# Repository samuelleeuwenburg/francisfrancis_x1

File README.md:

# FrancisFrancis X1

## Building the binary

Create a build folder, run cmake with your wifi info and build the project
```
$ mkdir firmware/build && cd firmware/build
$ cmake .. -DWIFI_SSID="network_name" -DWIFI_PASSWORD="password"
$ make -j4
```

## Running

Run openocd in the firmware folder
```
$ (sudo) openocd
```

Then use gdb to load the code
```
$ arm-none-eabi-gdb -q -x openocd.gdb build/francisfrancisx1.elf 
```

## Livebook

To run the notebook without installing Livebook you can use docker
```
$ docker run -p 8080:8080 -p 8081:8081 --pull always -u $(id -u):$(id -g) -v $(pwd):/data ghcr.io/livebook-dev/livebook
```

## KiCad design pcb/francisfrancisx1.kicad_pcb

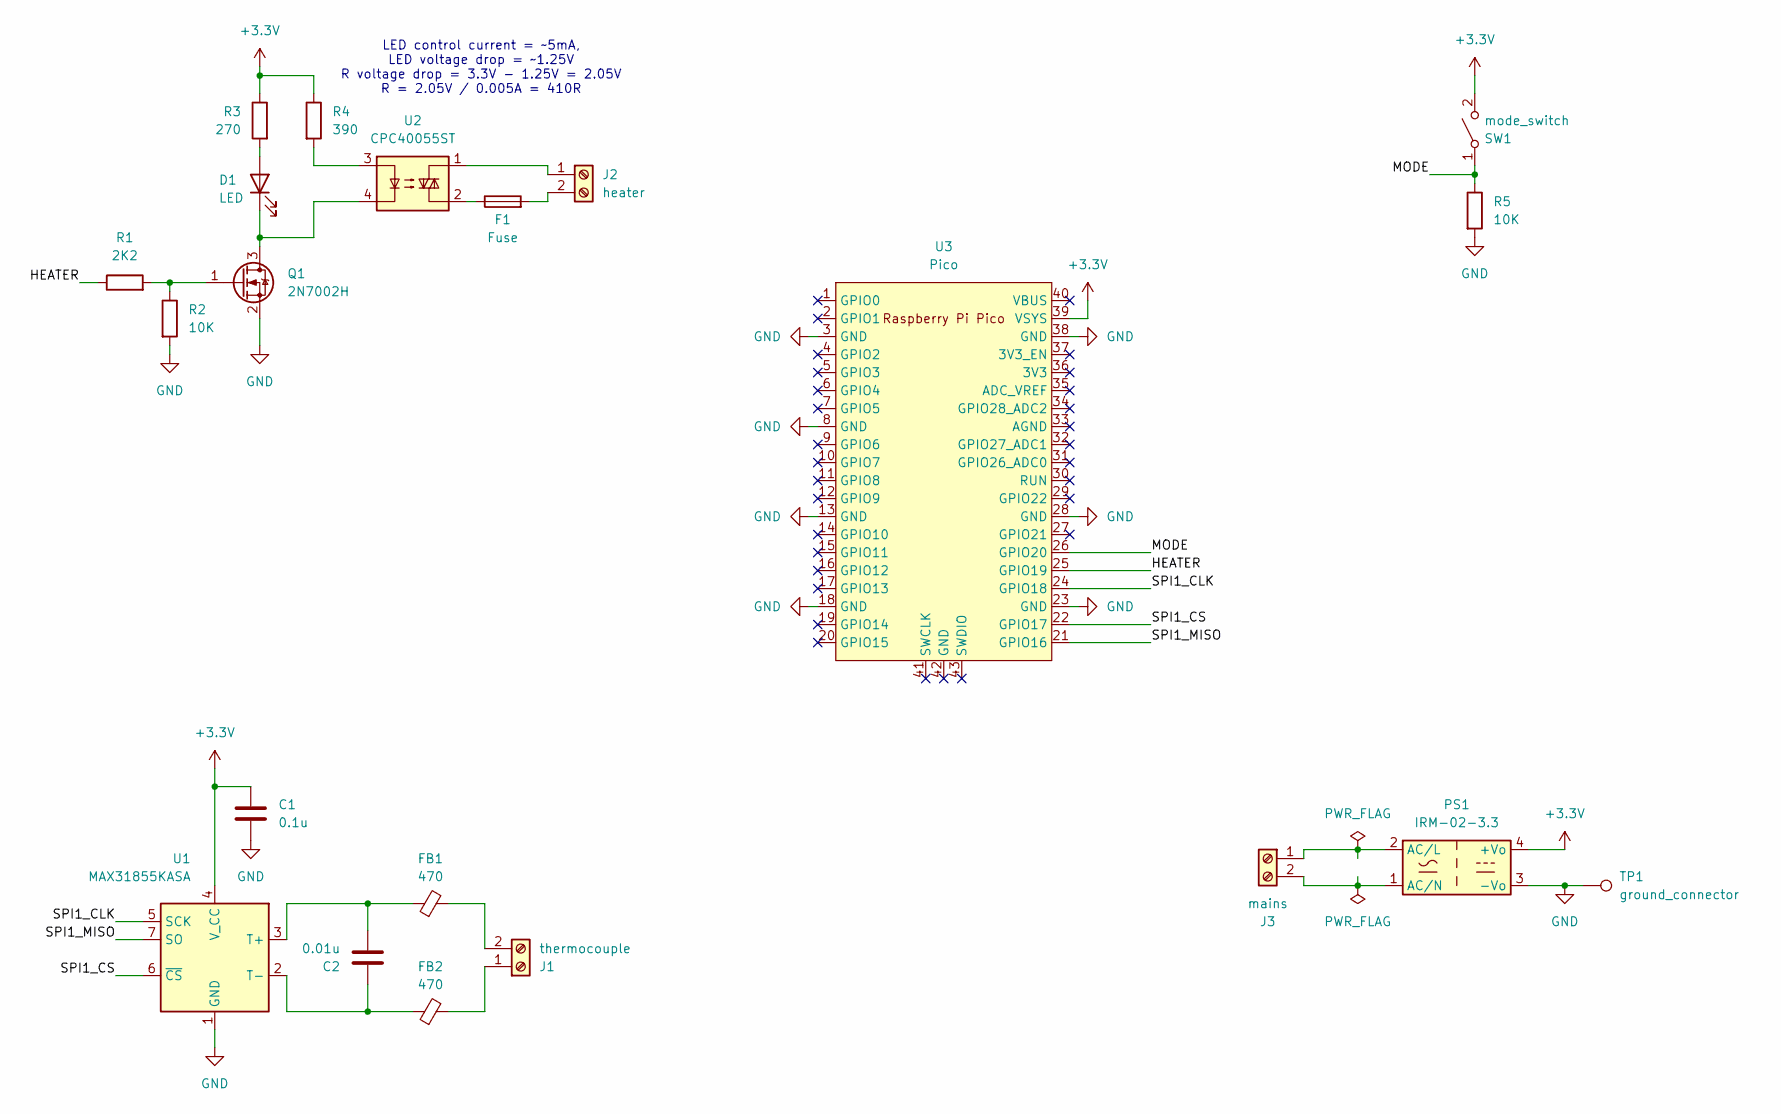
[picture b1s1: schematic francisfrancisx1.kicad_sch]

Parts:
C1: 0.1u; C_0805_2012Metric; MPN C0805X104K5RAC
C2: 0.01u; C_0805_2012Metric; MPN C0805Y103K5RACTU
D1: LED; LED_0805_2012Metric; MPN 150080AS75000
F1: Fuse; Fuseholder_Cylinder-5x20mm_Schurter_0031_8201_Horizontal_Op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; MPN 0031.8201.G
FB1, FB2: 470; R_0805_2012Metric; MPN 742792037
J1: thermocouple; TerminalBlock_Phoenix_MPT-0,5-2-2.54_1x02_P2.54mm_Horizontal; MPN 1725656
J2: heater; TerminalBlock_Phoenix_MKDS-1,5-2-5.08_1x02_P5.08mm_Horizont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; MPN 1715721
J3: mains; TerminalBlock_Phoenix_MKDS-1,5-2-5.08_1x02_P5.08mm_Horizont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; MPN 1715721
PS1: IRM-02-3.3; Converter_ACDC_MeanWell_IRM-02-xx_THT; MPN IRM-02-3.3
Q1: 2N7002H; SOT-23; MPN 2N7002HR
R1: 2K2; R_0805_2012Metric; MPN RT0805FRE132K2L
R2, R5: 10K; R_0805_2012Metric; MPN RT0805FRE1010KL
R3: 270; R_0805_2012Metric; MPN RT0805FRE07270RL
R4: 390; R_0805_2012Metric; MPN RT0805FRE07390RL
SW1: mode_switch; TerminalBlock_Phoenix_MPT-0,5-2-2.54_1x02_P2.54mm_Horizontal; MPN 1725656
TP1: ground_connector; MountingHole_2.2mm_M2_ISO7380_Pad
U1: MAX31855KASA; SOIC-8_3.9x4.9mm_P1.27mm; MPN MAX31855KASA+T
U2: CPC40055ST; MPN CPC40055ST
U3: Pico; RPi_Pico_SMD_TH; MPN SC0918

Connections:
+3.3V: C1.1, PS1.4 (+Vo), R3.1, R4.1, SW1.2 (B), U1.4 (V_CC), U3.39 (VSYS)
/HEATER: R1.1, U3.25 (GPIO19)
/MODE: R5.1, SW1.1 (A), U3.26 (GPIO20)
/SPI1_CLK: U1.5 (SCK), U3.24 (GPIO18)
/SPI1_CS: U1.6 (~CS), U3.22 (GPIO17)
/SPI1_MISO: U1.7 (SO), U3.21 (GPIO16)
GND: C1.2, PS1.3 (-Vo), Q1.2 (S), R2.2, R5.2, TP1.1, U1.1 (GND), U3.3 (GND), U3.8 (GND), U3.13 (GND), U3.18 (GND), U3.23 (GND), U3.28 (GND), U3.38 (GND)
unnamed: D1.2 (A), R3.2
unnamed: D1.1 (K), Q1.3 (D), U2.4
unnamed: F1.1, U2.2
unnamed: FB2.2, J1.1
unnamed: FB1.2, J1.2
unnamed: J2.1, U2.1
unnamed: F1.2, J2.2
unnamed: J3.1, PS1.2 (AC/L)
unnamed: J3.2, PS1.1 (AC/N)
unnamed: Q1.1 (G), R1.2, R2.1
unnamed: R4.2, U2.3
unnamed: C2.2, FB1.1, U1.3 (T+)
unnamed: C2.1, FB2.1, U1.2 (T-)

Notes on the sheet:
LED control current = ~5mA, LED voltage drop = ~1.25V R voltage drop = 3.3V - 1.25V = 2.05V R = 2.05V / 0.005A = 410R

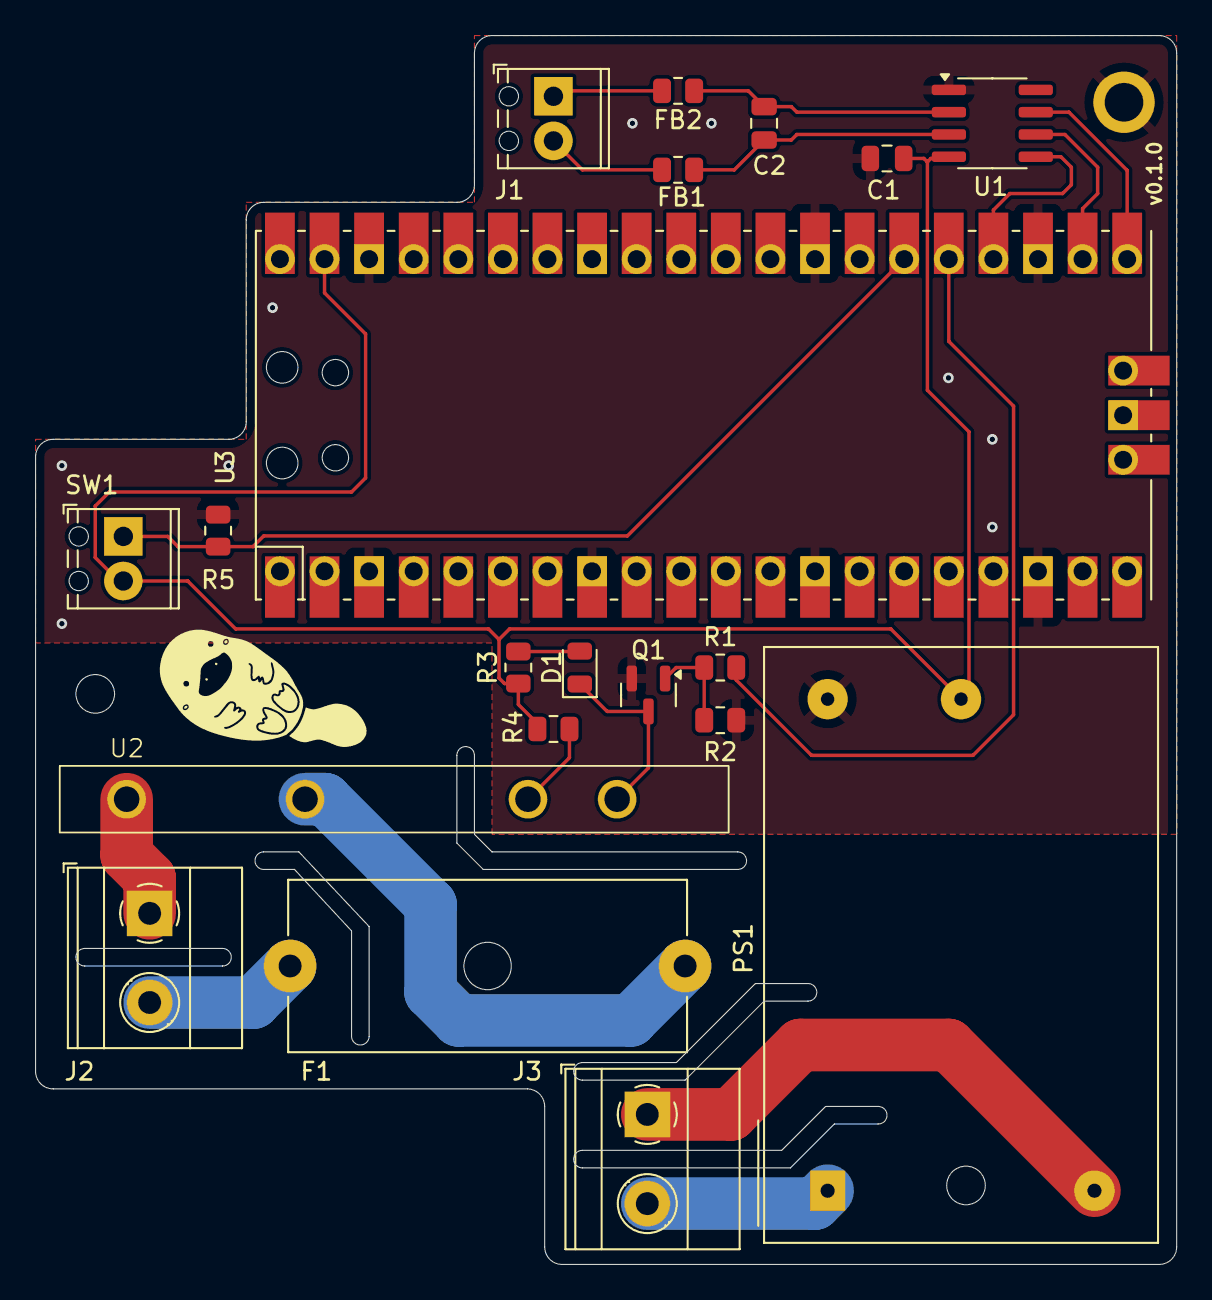
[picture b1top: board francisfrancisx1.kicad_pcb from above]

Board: 2 copper layers, 65.0 x 70.0 mm, 21 parts (0 on the bottom side), 20 nets.

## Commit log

2024-07-19 Version 0.1.0
